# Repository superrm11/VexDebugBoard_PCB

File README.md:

# _VexDebugBoard PCB_

This is the main hardware repository for the V5 Debug Board: a board designed to slot into the VEX V5 Smart Port, 
and transmit debug data over a websocket to a laptop. The data is received by a [Foxglove application](https://foxglove.dev) instance or ROS RViz, and allows for:

- 3D visualization of Odometry
- Real-time graphing for robot tuning
- Wireless print statements

This repository contains the circuit diagram, BOM and PCB layout for the board. 

## Pinout
Smart Port RX (from Brain): GPIO7  
Smart Port TX (to Brain): GPIO6  
RS485 Mode (TX=ON, RX=OFF): GPIO10  
STAT LED: GPIO4  
DBG_LED: GPIO18  
SD SPI MISO: GPIO0  
SD SPI MOSI: GPIO1  
SD SPI CS: GPIO3  
SD SPI SCL: GPIO19  

## Image Library

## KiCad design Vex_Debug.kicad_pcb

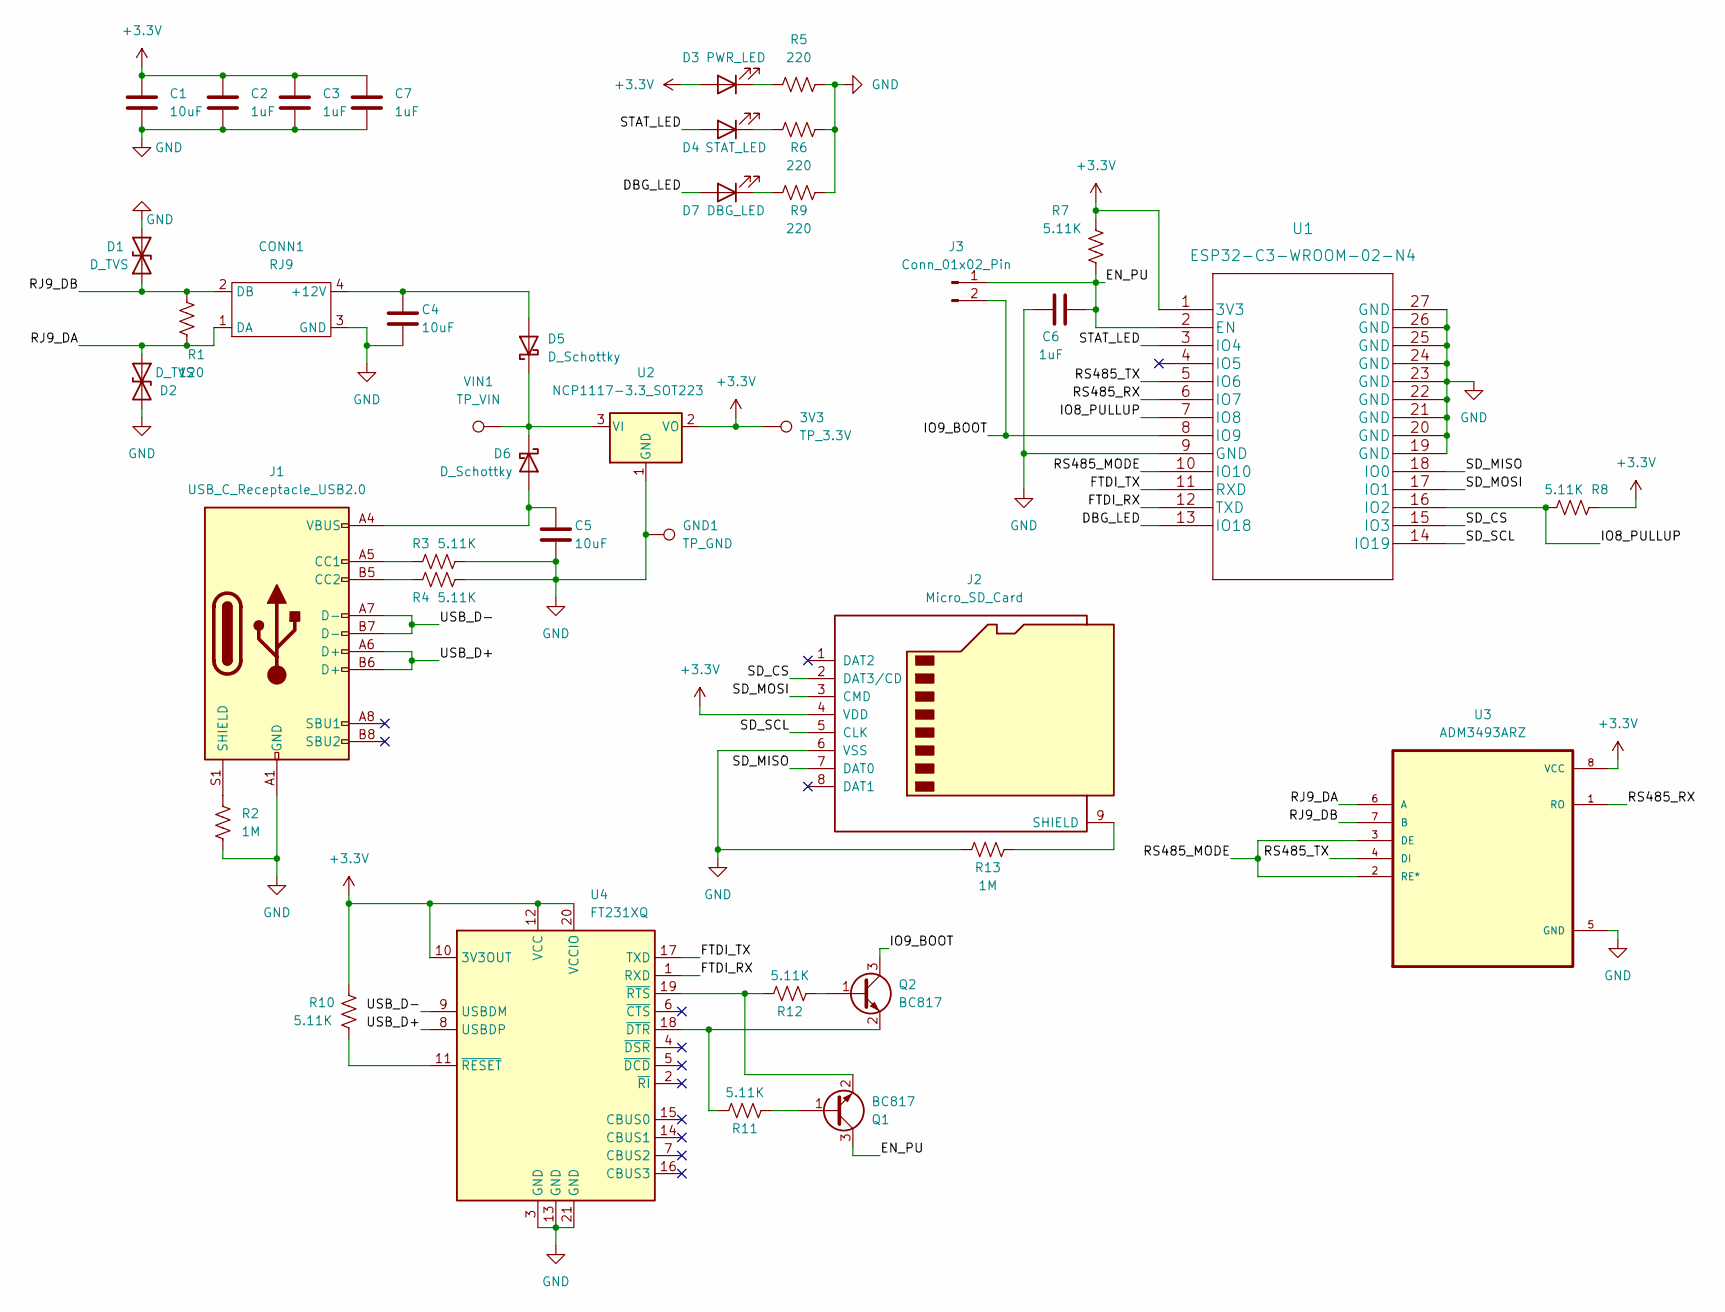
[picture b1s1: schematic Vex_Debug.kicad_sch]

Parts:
3V3: TP_3.3V; TestPoint_Pad_D1.5mm
C1, C4, C5: 10uF; C_0805_2012Metric_Pad1.18x1.45mm_HandSolder
C2, C3, C6, C7: 1uF; C_0805_2012Metric_Pad1.18x1.45mm_HandSolder
CONN1: RJ9; RJ9_Jack
D1, D2: D_TVS; D_SMA_Handsoldering
D3: PWR_LED; LED_0805_2012Metric_Pad1.15x1.40mm_HandSolder
D4: STAT_LED; LED_0805_2012Metric_Pad1.15x1.40mm_HandSolder
D5, D6: D_Schottky; D_SOD-323_HandSoldering
D7: DBG_LED; LED_0805_2012Metric_Pad1.15x1.40mm_HandSolder
GND1: TP_GND; TestPoint_Pad_D1.5mm
J1: USB_C_Receptacle_USB2.0; USB_C_Receptacle_GCT_USB4085
J2: Micro_SD_Card; microSD_HC_Molex_47219-2001
J3: Conn_01x02_Pin; PinHeader_1x02_P2.54mm_Vertical
Q1, Q2: BC817; SOT-23
R1: 120; R_0805_2012Metric_Pad1.20x1.40mm_HandSolder
R2, R13: 1M; R_0805_2012Metric_Pad1.20x1.40mm_HandSolder
R3, R4, R7, R8, R10, R11, R12: 5.11K; R_0805_2012Metric_Pad1.20x1.40mm_HandSolder
R5, R6, R9: 220; R_0805_2012Metric_Pad1.20x1.40mm_HandSolder
U1: ESP32-C3-WROOM-02-N4
U2: NCP1117-3.3_SOT223; SOT-223-3_TabPin2
U3: ADM3493ARZ; SOIC127P600X175-8N
U4: FT231XQ; QFN-20-1EP_4x4mm_P0.5mm_EP2.5x2.5mm
VIN1: TP_VIN; TestPoint_Pad_D1.5mm

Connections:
+3.3V: 3V3.1, C1.1, C2.1, C3.1, C7.1, D3.2 (A), J2.4 (VDD), R7.2, R8.2, R10.2, U1.1 (3V3), U2.2 (VO), U3.8 (VCC), U4.10 (3V3OUT), U4.12 (VCC), U4.20 (VCCIO)
/DBG_LED: D7.2 (A), U1.13 (IO18)
/EN_PU: C6.1, J3.1, Q1.3 (C), R7.1, U1.2 (EN)
/FTDI_RX: U1.12 (TXD), U4.1 (RXD)
/FTDI_TX: U1.11 (RXD), U4.17 (TXD)
/IO8_PULLUP: R8.1, U1.7 (IO8), U1.16 (IO2)
/IO9_BOOT: J3.2, Q2.3 (C), U1.8 (IO9)
/RJ9_DA: CONN1.1 (DA), D2.1 (A1), R1.2, U3.6 (A)
/RJ9_DB: CONN1.2 (DB), D1.1 (A1), R1.1, U3.7 (B)
/RS485_MODE: U1.10 (IO10), U3.2 (RE*), U3.3 (DE)
/RS485_RX: U1.6 (IO7), U3.1 (RO)
/RS485_TX: U1.5 (IO6), U3.4 (DI)
/SD_CS: J2.2 (DAT3/CD), U1.15 (IO3)
/SD_MISO: J2.7 (DAT0), U1.18 (IO0)
/SD_MOSI: J2.3 (CMD), U1.17 (IO1)
/SD_SCL: J2.5 (CLK), U1.14 (IO19)
/STAT_LED: D4.2 (A), U1.3 (IO4)
/USB_D+: J1.A6 (D+), J1.B6 (D+), U4.8 (USBDP)
/USB_D-: J1.A7 (D-), J1.B7 (D-), U4.9 (USBDM)
GND: C1.2, C2.2, C3.2, C4.2, C5.2, C6.2, C7.2, CONN1.3 (GND), D1.2 (A2), D2.2 (A2), GND1.1, J1.A1 (GND), J1.A12 (GND), J1.B1 (GND), J1.B12 (GND), J2.6 (VSS), R2.2, R3.2, R4.2, R5.2, R6.2, R9.2, R13.2, U1.9 (GND), U1.19 (GND), U1.20 (GND), U1.21 (GND), U1.22 (GND), U1.23 (GND), U1.24 (GND), U1.25 (GND), U1.26 (GND), U1.27 (GND), U2.1 (GND), U3.5 (GND), U4.3 (GND), U4.13 (GND), U4.21 (GND); also elsewhere on the board
unnamed: C4.1, CONN1.4 (+12V), D5.2 (A)
unnamed: D3.1 (K), R5.1
unnamed: D4.1 (K), R6.1
unnamed 23: D5.1 (K), D6.1 (K), U2.3 (VI), VIN1.1; also elsewhere on the board
unnamed: C5.1, D6.2 (A), J1.A4 (VBUS), J1.A9 (VBUS), J1.B4 (VBUS), J1.B9 (VBUS)
unnamed: D7.1 (K), R9.1
unnamed: J1.A5 (CC1), R3.1
unnamed: J1.B5 (CC2), R4.1
unnamed: J1.S1 (SHIELD), R2.1
unnamed: J2.9 (SHIELD), R13.1
unnamed: Q1.1 (B), R11.2
unnamed: Q1.2 (E), R12.1, U4.19 (~RTS)
unnamed: Q2.1 (B), R12.2
unnamed: Q2.2 (E), R11.1, U4.18 (~DTR)
unnamed: R10.1, U4.11 (~RESET)

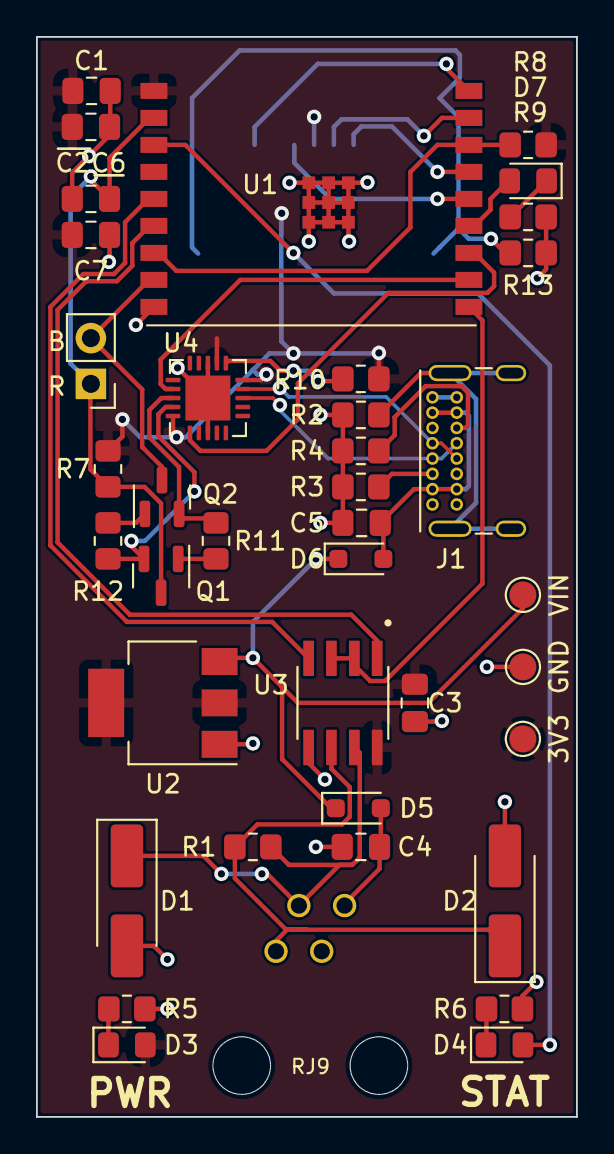
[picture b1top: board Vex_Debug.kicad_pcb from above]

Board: 2 copper layers, 30.0 x 60.0 mm, 40 parts (1 on the bottom side), 35 nets.

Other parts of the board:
GND: TP_GND; TestPoint_Pad_D1.5mm
VIN: TP_VIN; TestPoint_Pad_D1.5mm

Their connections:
GND: GND.1; also elsewhere on the board
unnamed 23: VIN.1; also elsewhere on the board

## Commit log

2022-11-13 Revision 1 (ESP32-C3-MINI)
2022-11-28 Revision 2.1 release
2022-11-28 Added images
2022-11-28 Create LICENSE
2024-01-22 Updated to revision 3.0

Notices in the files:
parts and their libraries:
Copyright 2021 Accelerated Designs. All rights reserved.
